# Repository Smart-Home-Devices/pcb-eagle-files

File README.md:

# Eagle Files for the PCB
Repo contains all the eagle files for custom designed relay module.

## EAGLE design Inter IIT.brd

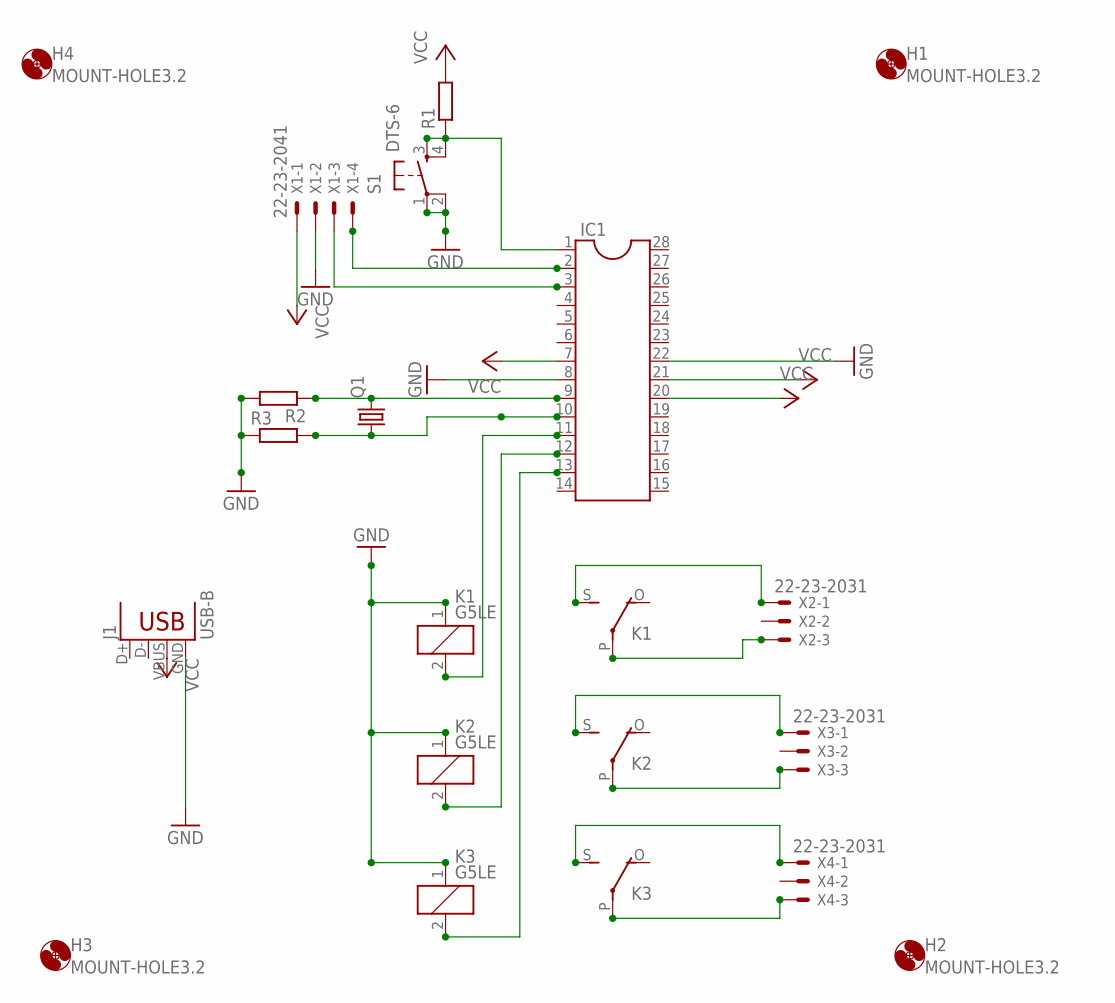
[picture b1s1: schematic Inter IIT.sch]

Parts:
H1, H2, H3, H4: MOUNT-HOLE3.2; 3,2
IC1: DIL28-3
J1: USB-B; USB-B-PTH
K1, K2, K3: G5LE
Q1: CRYSTALHC49S; HC49/S
R1, R2, R3: RESISTOR7.5MM
S1: DTS-6
X1: 22-23-2041
X2, X3, X4: 22-23-2031

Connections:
GND: IC1.8, IC1.22, J1.GND, K1.1, K2.1, K3.1, R2.2, R3.1, S1.1, S1.2, X1.2
unnamed: IC1.2, X1.4
unnamed: IC1.3, X1.3
unnamed: IC1.1, R1.1, S1.3, S1.4
unnamed: IC1.9, Q1.2, R2.1
unnamed: IC1.12, K2.2
unnamed: IC1.11, K1.2
unnamed: IC1.10, Q1.1, R3.2
unnamed: IC1.13, K3.2
unnamed: K1.S, X2.1
unnamed: K1.P, X2.3
unnamed: K2.S, X3.1
unnamed: K2.P, X3.3
unnamed: K3.S, X4.1
unnamed: K3.P, X4.3
VCC: IC1.7, IC1.20, IC1.21, J1.VBUS, R1.2, X1.1

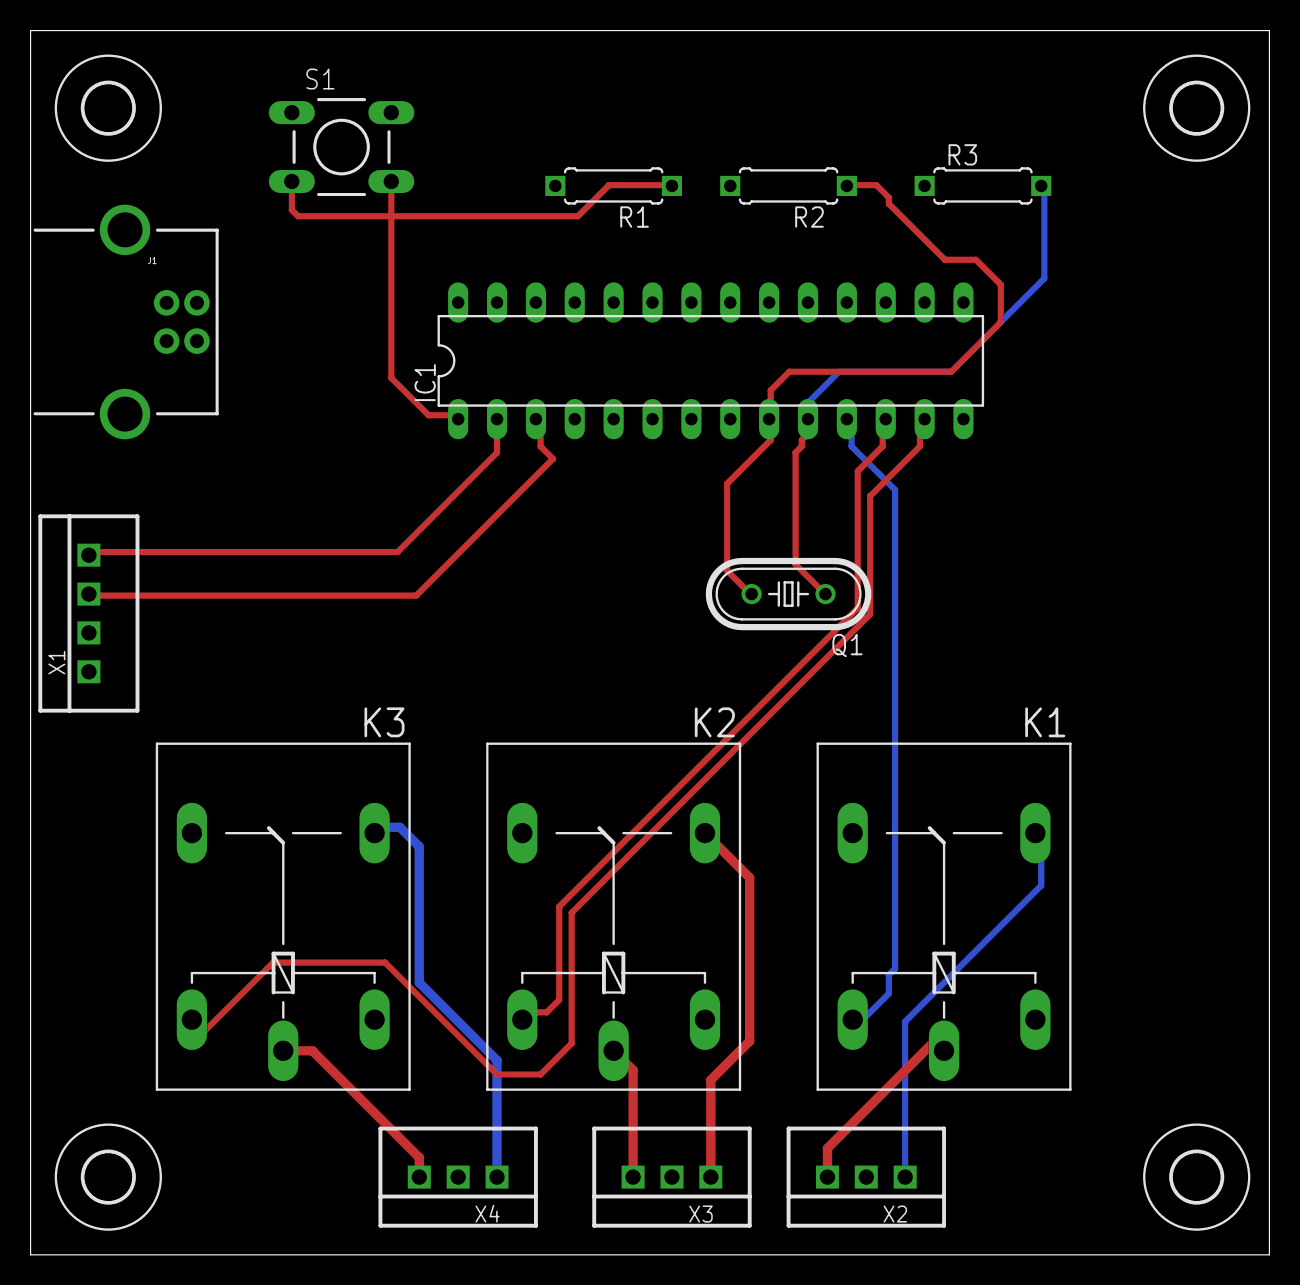
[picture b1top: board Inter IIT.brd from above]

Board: 2 copper layers, 81.0 x 80.0 mm, 18 parts (0 on the bottom side), 16 nets.

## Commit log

2016-03-29 Add README.md

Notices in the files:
parts and their libraries:
SparkFun-Connectors: Licensing: Creative Commons ShareAlike 4.0 International - https://creativecommons.org/licenses/by-sa/4.0
